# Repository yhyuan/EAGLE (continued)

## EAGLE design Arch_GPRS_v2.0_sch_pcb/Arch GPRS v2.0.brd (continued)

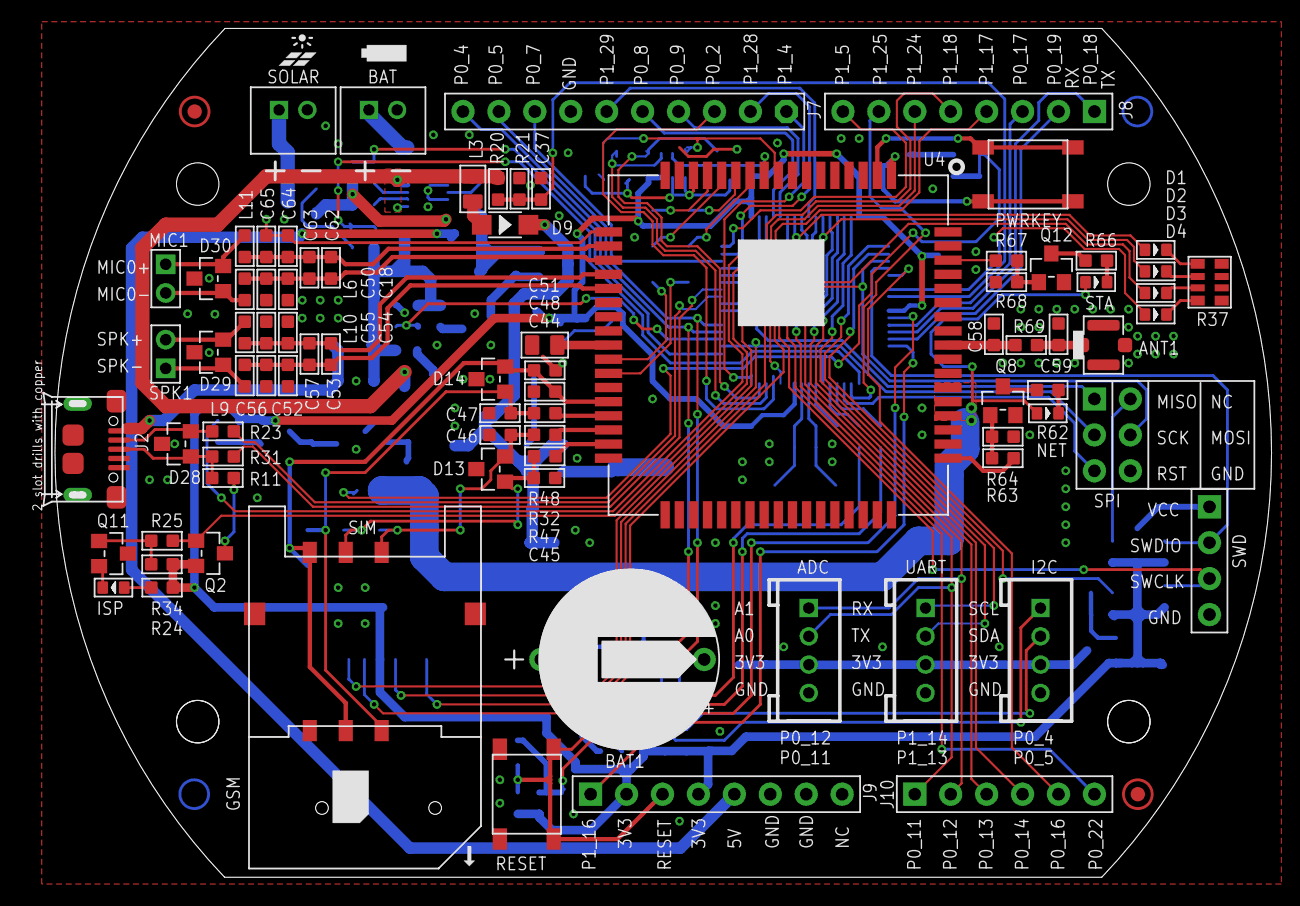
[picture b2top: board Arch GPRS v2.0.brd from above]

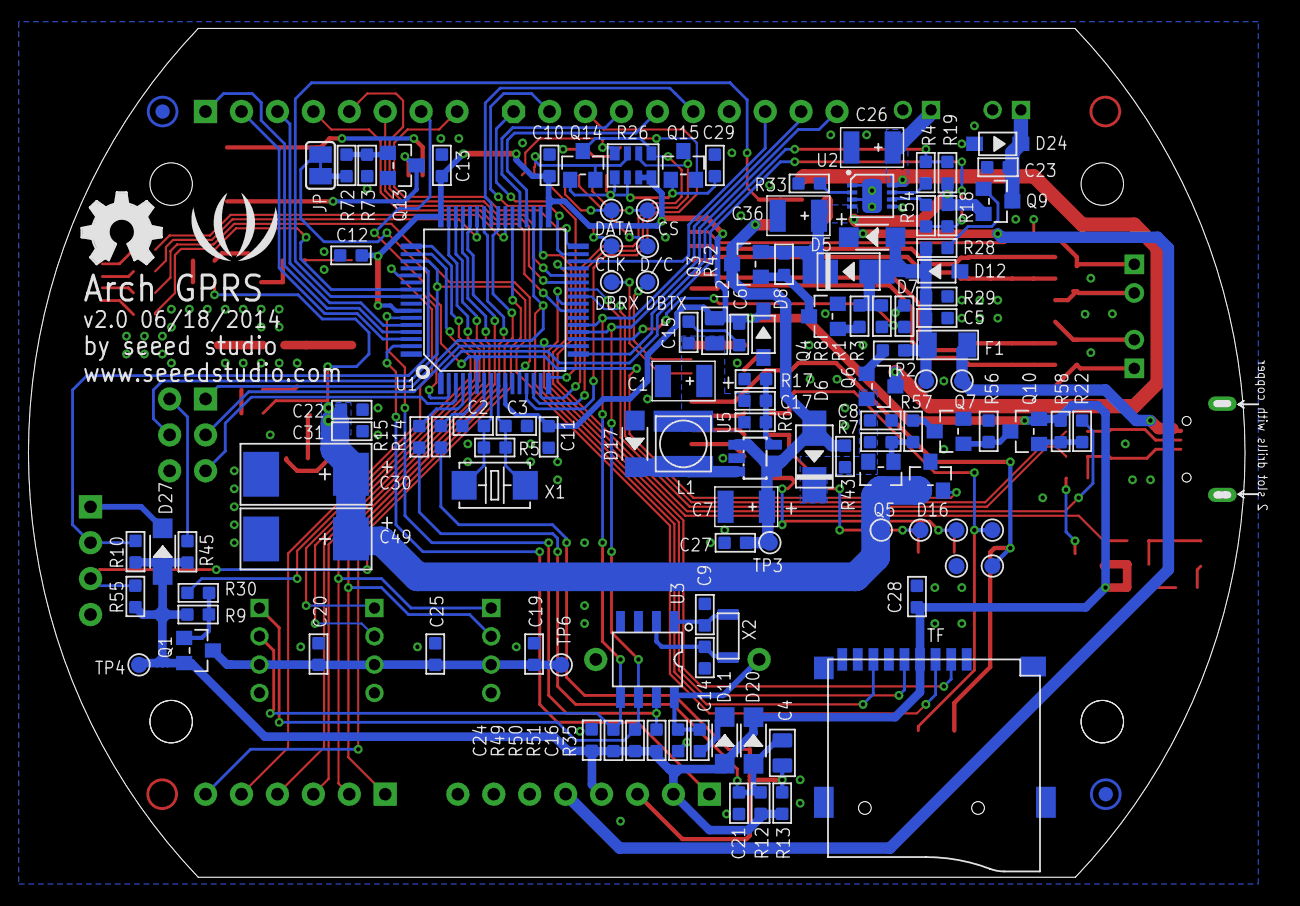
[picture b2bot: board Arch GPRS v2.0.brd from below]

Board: 2 copper layers, 86.9 x 60.0 mm, 207 parts (123 on the bottom side), 139 nets.

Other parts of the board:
U$55: LOGO_SILK
U$56: OSHW_FILLX200_NOTEXT

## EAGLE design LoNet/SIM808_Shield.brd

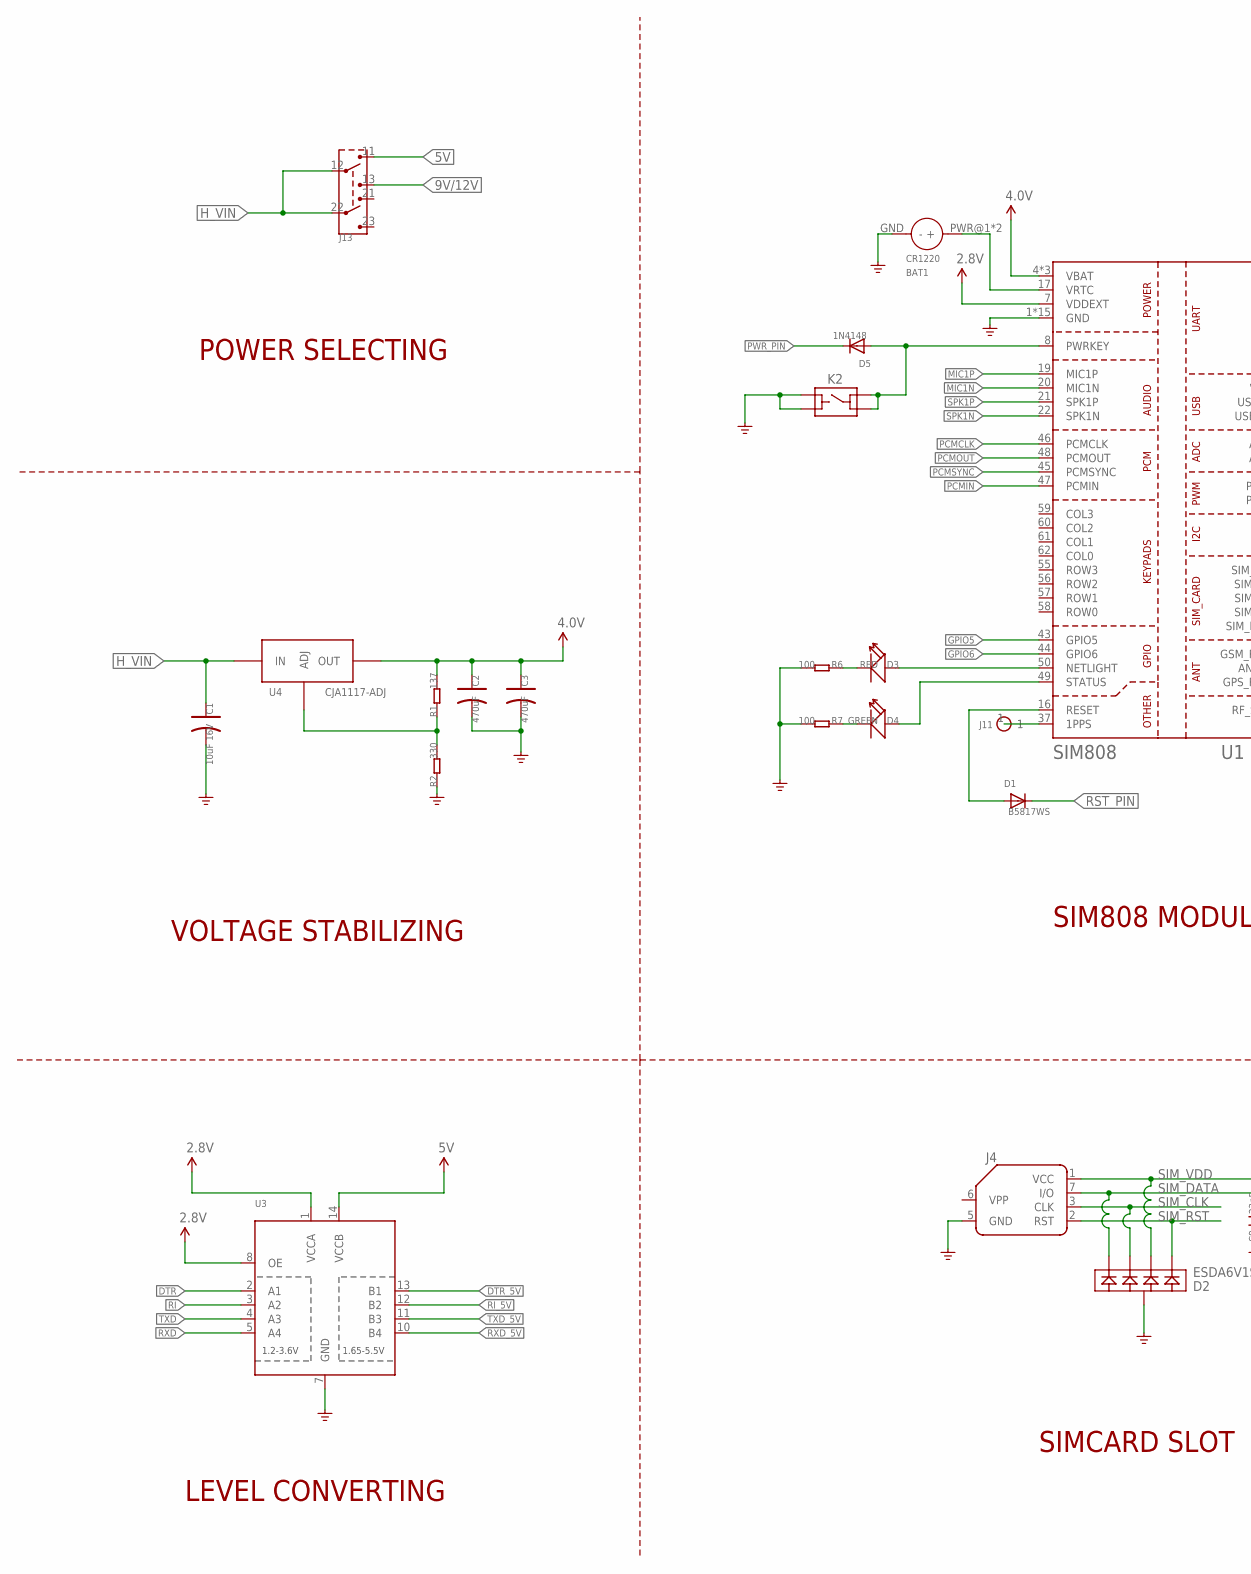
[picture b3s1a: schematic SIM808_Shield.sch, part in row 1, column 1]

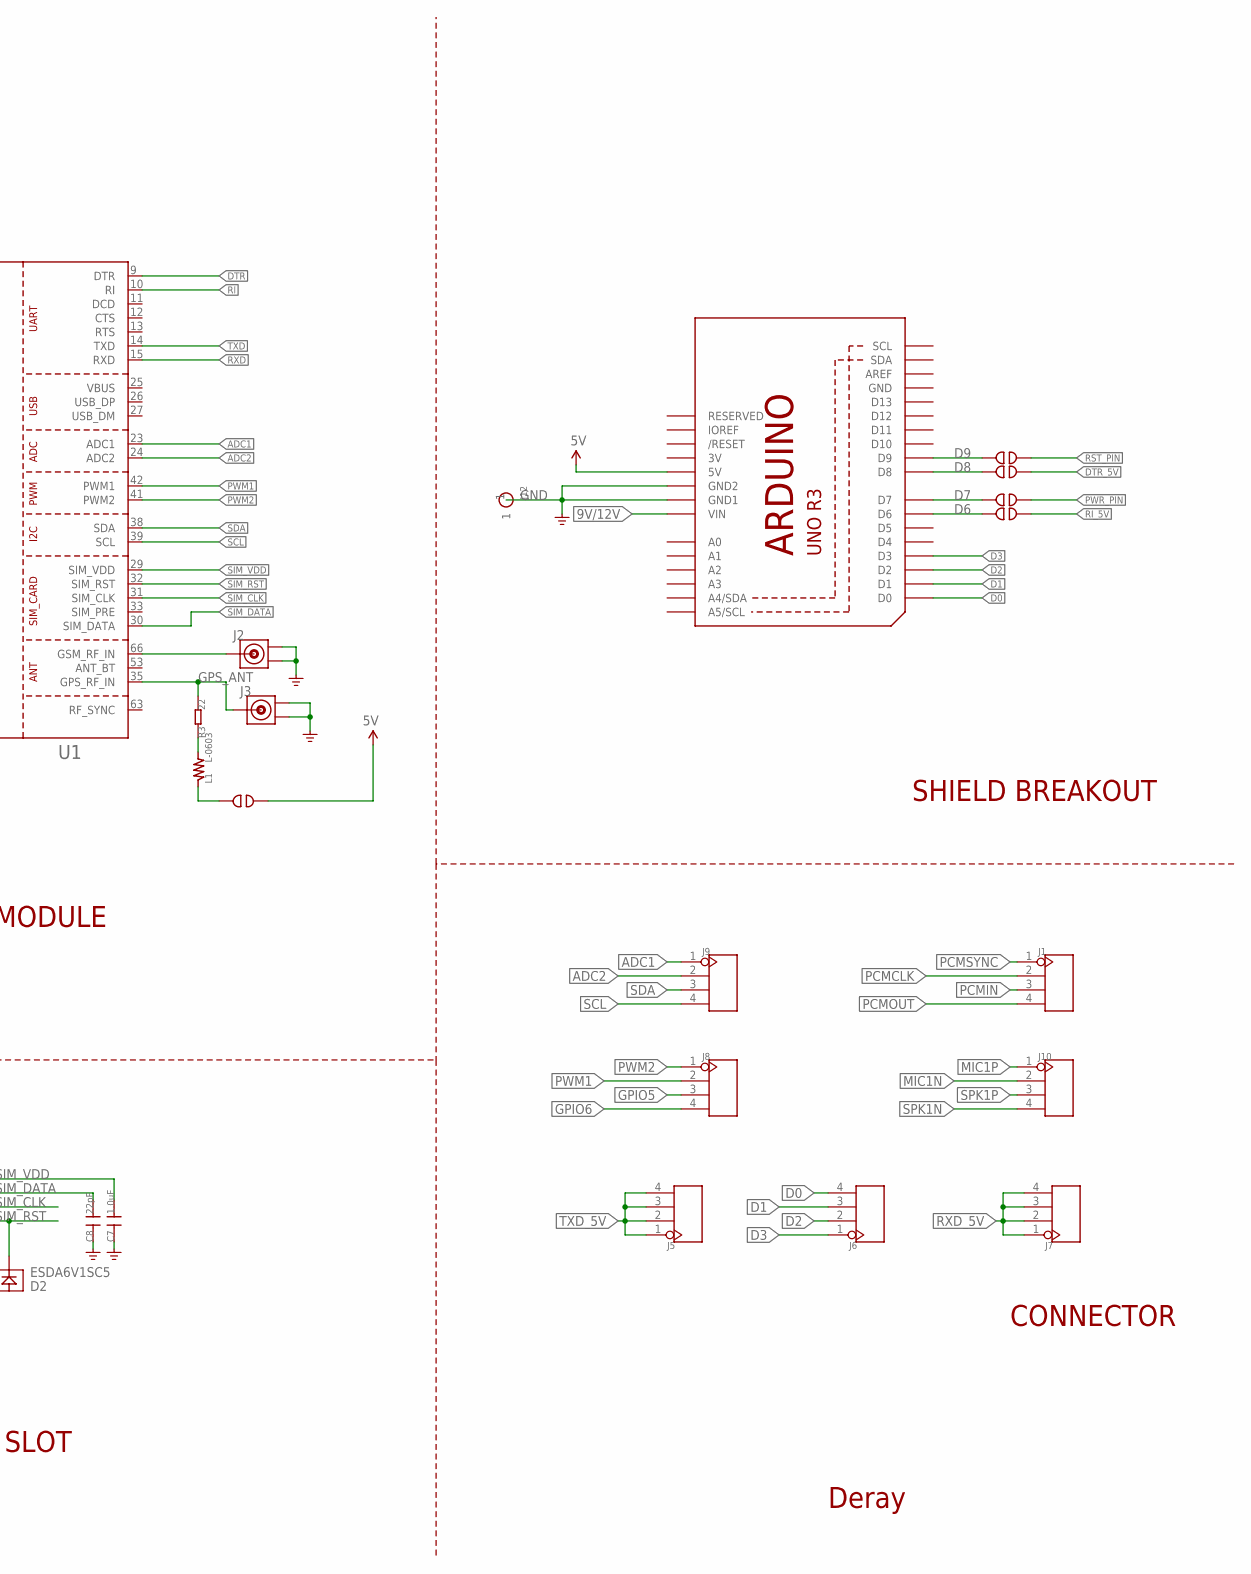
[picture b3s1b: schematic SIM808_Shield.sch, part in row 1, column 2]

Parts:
BAT1: CR1220; BATTCON_12MM
C1: 10uF 16V; AVX-A
C2, C3: 470uF; AVX-D
C7: 1.0uF; 0603
C8: 22pF; 0603
D1: B5817WS; SOD-323F
D2: ESDA6V1SC5; SOT23-5L
D3: RED; 0603
D4: GREEN; 0603
D5: 1N4148; SOD-323F
J1, J5, J6, J7, J8, J9, J10: HEADER-4P-80/40MIL; 4P-2.54-80/40MIL
J2, J3: ANTENNA-U-FL'3PAD-TYPE'; 3P-U-FL
J4: SIMHOLDERSIM; SIMHOLDER
J11, J12: HEADER-1P-40; 1P-80/40MIL
J13: SWITCH-6P-SMD
K2: BUTTON-4P-6X6-SMD; 4P-SMD-6.2X6.2X4H
L1: L-0603; 0603
R1: 137; 0603
R2: 330; 0603
R3: 22; 0603
R6, R7: 100; 0603
U1: SIM808; 68P-24X24X2.6
U2: ARDUINOR3-DIMENSION; ARDUINOR3
U3: TXB0104PWR; TSSOP14
U4: CJA1117-ADJ; SOT89
U$8, U$17, U$18, U$19, U$20: 2P-DISABLE

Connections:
2.8V: U1.7 (VDDEXT), U3.1 (VCCA), U3.8 (OE)
3V: U2.3V
4.0V: C2.+, C3.+, R1.2, U1.4 (VBAT), U1.5 (VBAT), U1.6 (VBAT), U4.2 (OUT), U4.4 (OUT)
5V: J13.11, U2.5V, U3.14 (VCCB), U$17.P$2
9V/12V: J13.13, U2.VIN
ADC1: J9.1, U1.23 (ADC1)
ADC2: J9.2, U1.24 (ADC2)
D0: J6.4, U2.D0
D1: J6.3, U2.D1
D2: J6.2, U2.D2
D3: J6.1, U2.D3
D6: U2.D6, U$20.P$1
D7: U2.D7, U$19.P$1
D8: U2.D8, U$18.P$1
D9: U2.D9, U$8.P$1
DTR: U1.9 (DTR), U3.2 (A1)
DTR_5V: U3.13 (B1), U$18.P$2
GND: BAT1.GND (-), C1.-, C2.-, C3.-, C7.1, C8.1, D2.2, J2.GND1, J2.GND2, J3.GND1, J3.GND2, J4.5 (GND), J12.1, K2.2 (B0), K2.3 (B1), R2.1, R6.2, R7.2, U1.1 (GND), U1.2 (GND), U1.3 (GND), U1.18 (GND), U1.28 (GND), U1.34 (GND), U1.36 (GND), U1.40 (GND), U1.51 (GND), U1.52 (GND), U1.54 (GND), U1.64 (GND), U1.65 (GND), U1.67 (GND), U1.68 (GND), U2.GND, U2.GND1, U2.GND2, U3.7 (GND)
GPIO5: J8.3, U1.43 (GPIO5)
GPIO6: J8.4, U1.44 (GPIO6)
GPS_ANT: J3.D, R3.2, U1.35 (GPS_RF_IN)
H_VIN: C1.+, J13.12, J13.22, U4.3 (IN)
MIC1N: J10.2, U1.20 (MIC1N)
MIC1P: J10.1, U1.19 (MIC1P)
unnamed: BAT1.PWR@1 (+), BAT1.PWR@2 (+), U1.17 (VRTC)
unnamed: J2.D, U1.66 (GSM_RF_IN)
unnamed: R1.1, R2.2, U4.1 (ADJ)
unnamed: D1.A, U1.16 (RESET)
unnamed: J11.1, U1.37 (1PPS)
unnamed: D4.-, R7.1
unnamed: D5.A, K2.1 (A0), K2.4 (A1), U1.8 (PWRKEY)
unnamed: D3.-, R6.1
unnamed: D4.+, U1.49 (STATUS)
unnamed: D3.+, U1.50 (NETLIGHT)
unnamed: L1.1, U$17.P$1
unnamed: L1.2, R3.1
PCMCLK: J1.2, U1.46 (PCMCLK)
PCMIN: J1.3, U1.47 (PCMIN)
PCMOUT: J1.4, U1.48 (PCMOUT)
PCMSYNC: J1.1, U1.45 (PCMSYNC)
PWM1: J8.2, U1.42 (PWM1)
PWM2: J8.1, U1.41 (PWM2)
PWR_PIN: D5.C, U$19.P$2
RI: U1.10 (RI), U3.3 (A2)
RI_5V: U3.12 (B2), U$20.P$2
RST_PIN: D1.C, U$8.P$2
RXD: U1.15 (RXD), U3.5 (A4)
RXD_5V: J7.1, J7.2, J7.3, J7.4, U3.10 (B4)
SCL: J9.4, U1.39 (SCL)
SDA: J9.3, U1.38 (SDA)
SIM_CLK: D2.3, J4.3 (CLK), U1.31 (SIM_CLK)
SIM_DATA: C8.2, D2.1, J4.7 (I/O), U1.30 (SIM_DATA)
SIM_RST: D2.4, J4.2 (RST), U1.32 (SIM_RST)
SIM_VDD: C7.2, D2.5, J4.1 (VCC), U1.29 (SIM_VDD)
SPK1N: J10.4, U1.22 (SPK1N)
SPK1P: J10.3, U1.21 (SPK1P)
TXD: U1.14 (TXD), U3.4 (A3)
TXD_5V: J5.1, J5.2, J5.3, J5.4, U3.11 (B3)

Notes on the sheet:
POWER SELECTING
LEVEL CONVERTING
SIMCARD SLOT
SIM808 MODULE
CONNECTOR
SHIELD BREAKOUT
VOLTAGE STABILIZING
Deray

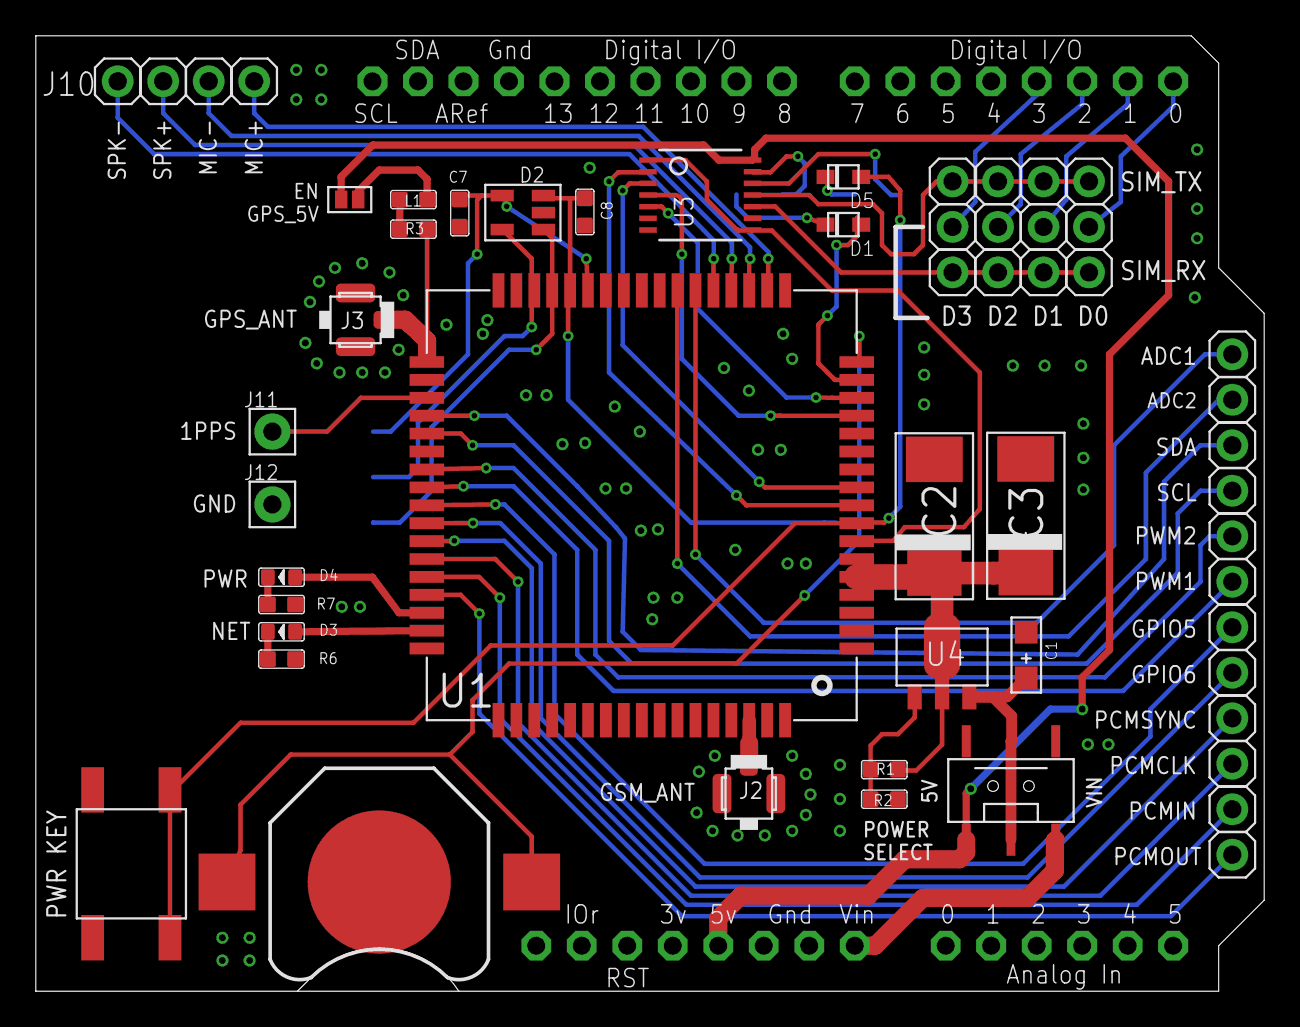
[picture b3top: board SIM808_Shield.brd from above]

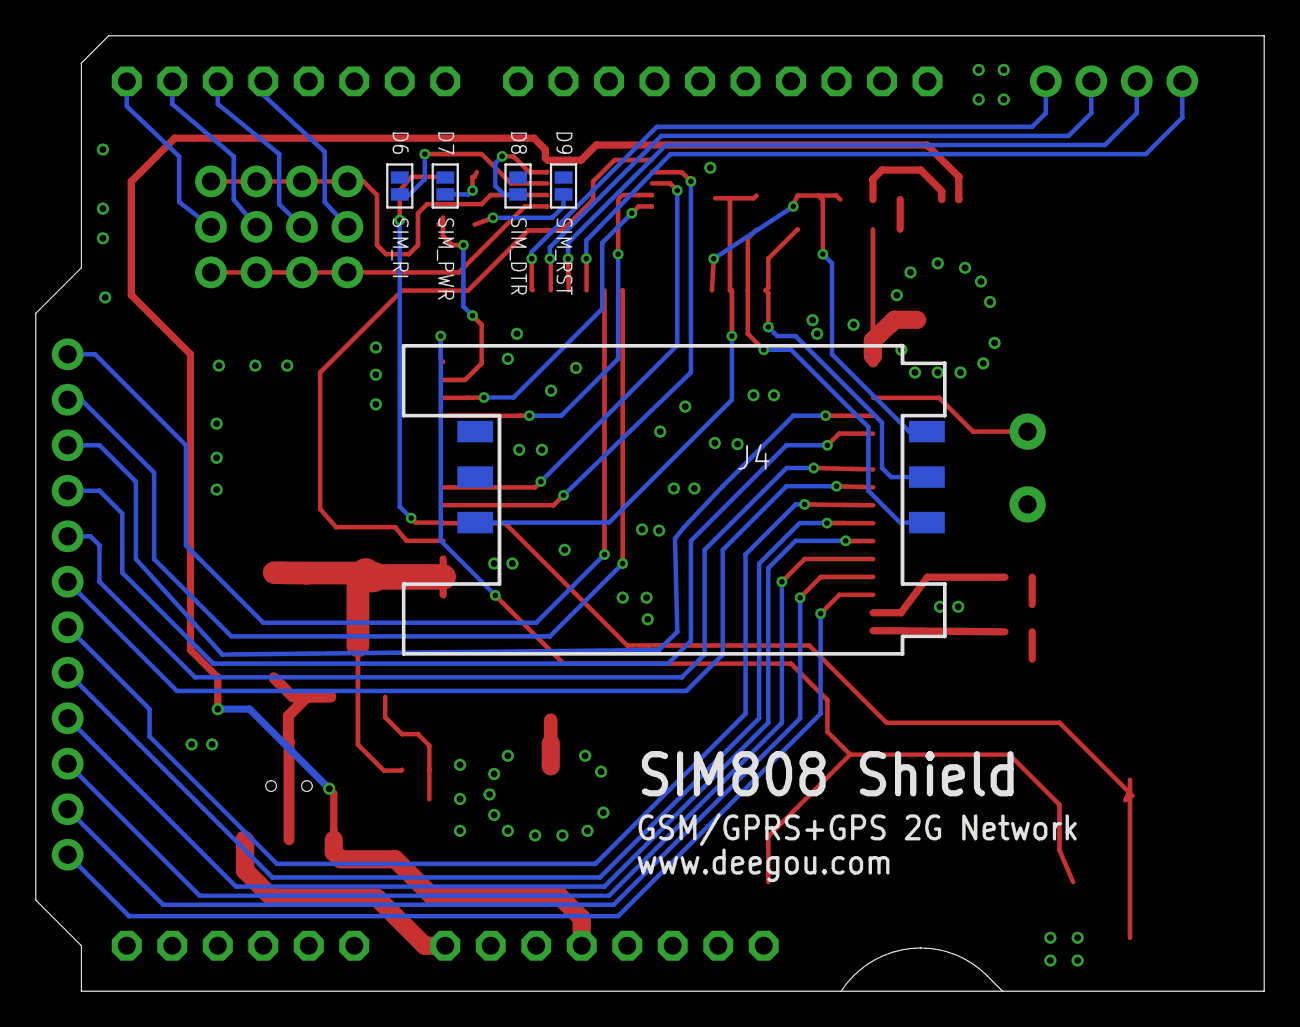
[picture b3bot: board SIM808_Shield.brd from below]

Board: 2 copper layers, 68.6 x 53.3 mm, 40 parts (5 on the bottom side), 57 nets.

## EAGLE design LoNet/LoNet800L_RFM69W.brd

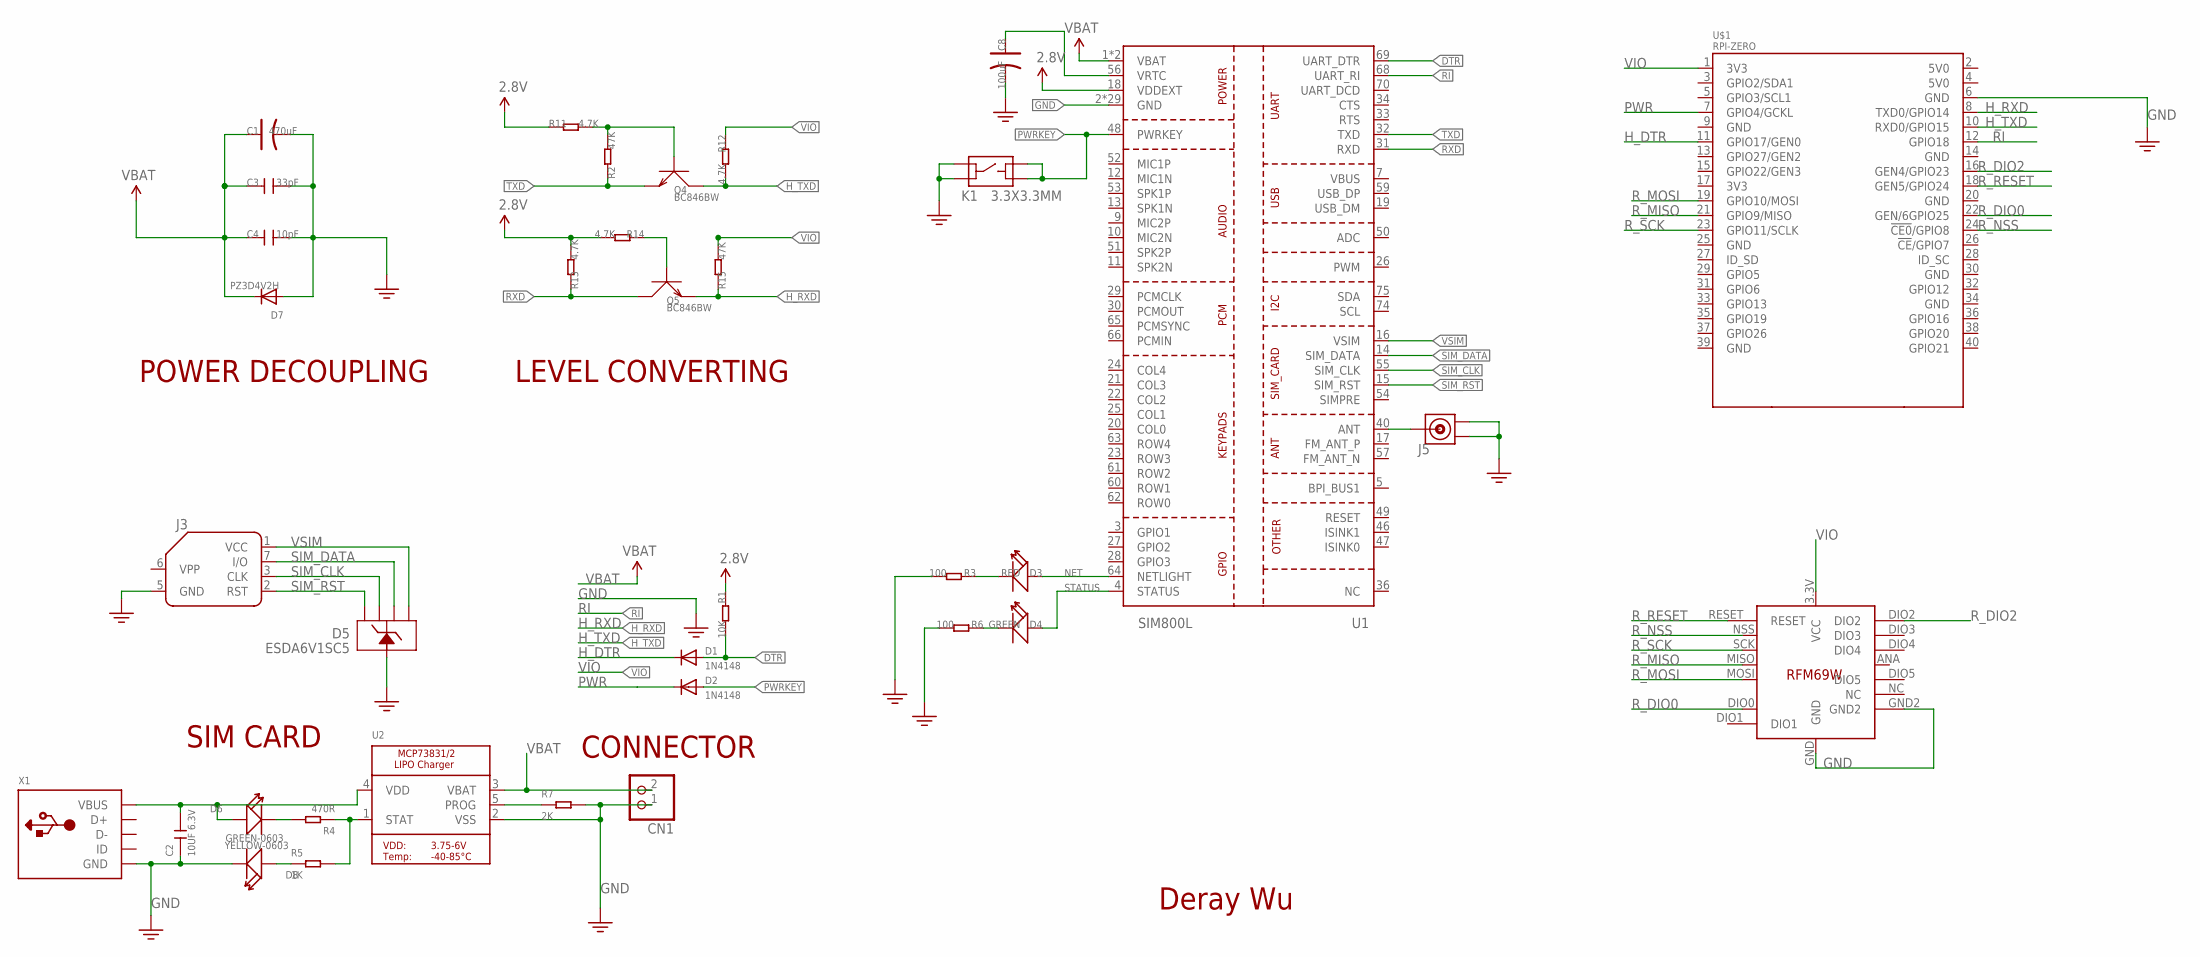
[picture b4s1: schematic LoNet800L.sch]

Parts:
C1: 470uF; AVX-D
C2: 10UF 6.3V; C0603
C3: 33pF; C0603
C4: 10pF; C0603
C8: 100uF; AVX-A
CN1: JST_2PIN; JSTPH2
D1, D2: 1N4148; SOD-323F
D3: RED; 0603
D4: GREEN; 0603
D5: ESDA6V1SC5; SOT23-5L
D6: YELLOW-0603; LED-0603
D7: PZ3D4V2H; SOD-323F
D8: GREEN-0603; LED-0603
J3: SIMHOLDERSIM; SIMHOLDER
J5: ANTENNA-U-FL'3PAD-TYPE'; 3P-U-FL
K1: 3.3X3.3MM; 4P-SMD-3.4X3.4X1.3H
Q4, Q5: BC846BW; SOT323
R1: 10K; 0603
R2, R15: 47K; 0603
R3, R6: 100; 0603
R4: 470R; R0603
R5: 1K; R0603
R7: 2K; R0603
R11, R12, R13, R14: 4.7K; 0603
U1: SIM800L; 88P-17.8X15.8X2.4
U2: MCP73831/2; SOT23-5
U$1: RPI-ZERO; RASPBERRYPI_BASTELSTUBE_V13_RASPI_BOARD_B+_FULL
U$2: RFM69; RFM69W-MINPADS
X1: USBMICRO_20329; 4UCONN_20329

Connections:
2.8V: R1.1, R11.1, R13.2, R14.2, U1.18 (VDDEXT)
ANT: J5.D, U1.40 (ANT)
DTR: D1.A, R1.2, U1.69 (UART_DTR)
GND: C1.-, C2.1, C3.2, C4.2, C8.-, CN1.1, D5.2, D7.A, D8.-, J3.5 (GND), J5.GND1, J5.GND2, K1.A0, K1.A1, R3.2, R6.2, R7.2, U1.2 (GND), U1.6 (GND), U1.8 (GND), U1.35 (GND), U1.37 (GND), U1.38 (GND), U1.39 (GND), U1.41 (GND), U1.43 (GND), U1.44 (GND), U1.45 (GND), U1.58 (GND), U1.67 (GND), U1.71 (GND), U1.72 (GND), U1.73 (GND), U1.76 (GND), U1.77 (GND), U1.78 (GND), U1.79 (GND), U1.80 (GND), U1.81 (GND), U1.82 (GND), U1.83 (GND), U1.84 (GND), U1.85 (GND), U1.86 (GND), U1.87 (GND), U1.88 (GND), U2.2 (VSS), U$1.6 (GND), U$2.GND, U$2.GND2, X1.BASE@1 (GND), X1.BASE@2 (GND), X1.GND, X1.SPRT@1 (GND), X1.SPRT@2 (GND), X1.SPRT@3 (GND), X1.SPRT@4 (GND)
H_DTR: D1.C, U$1.11 (GPIO17/GEN0)
H_RXD: Q5.2 (E), R15.1, U$1.8 (TXD0/GPIO14)
H_TXD: Q4.3 (C), R12.2, U$1.10 (RXD0/GPIO15)
unnamed: C8.+, U1.56 (VRTC)
unnamed: C2.2, D6.+, U2.4 (VDD), X1.VBUS
unnamed: D3.-, R3.1
unnamed: D6.-, R4.2
unnamed: Q4.1 (B), R2.2, R11.2
unnamed: R4.1, R5.2, U2.1 (STAT)
unnamed: D4.-, R6.1
unnamed: Q5.1 (B), R14.1
unnamed: D8.+, R5.1
unnamed: R7.1, U2.5 (PROG)
NET: D3.+, U1.64 (NETLIGHT)
PWR: D2.C, U$1.7 (GPIO4/GCKL)
PWRKEY: D2.A, K1.B0, K1.B1, U1.48 (PWRKEY)
RI: U1.68 (UART_RI), U$1.12 (GPIO18)
RXD: Q5.3 (C), R13.1, U1.31 (RXD)
R_DIO0: U$1.22 (GEN/6GPIO25), U$2.DIO0
R_DIO2: U$1.16 (GEN4/GPIO23), U$2.DIO2
R_MISO: U$1.21 (GPIO9/MISO), U$2.MISO
R_MOSI: U$1.19 (GPIO10/MOSI), U$2.MOSI
R_NSS: U$1.24 (!CE0!/GPIO8), U$2.NSS (SEL)
R_RESET: U$1.18 (GEN5/GPIO24), U$2.RESET
R_SCK: U$1.23 (GPIO11/SCLK), U$2.SCK
SIM_CLK: D5.5, J3.3 (CLK), U1.55 (SIM_CLK)
SIM_DATA: D5.3, J3.7 (I/O), U1.14 (SIM_DATA)
SIM_RST: D5.4, J3.2 (RST), U1.15 (SIM_RST)
STATUS: D4.+, U1.4 (STATUS)
TXD: Q4.2 (E), R2.1, U1.32 (TXD)
VBAT: C1.+, C3.1, C4.1, CN1.2, D7.C, U1.1 (VBAT), U1.42 (VBAT), U2.3 (VBAT)
VIO: R12.1, R15.2, U$1.1 (3V3), U$2.3.3V (VCC)
VSIM: D5.1, J3.1 (VCC), U1.16 (VSIM)

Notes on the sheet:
SIM CARD
POWER DECOUPLING
Deray Wu
CONNECTOR
LEVEL CONVERTING

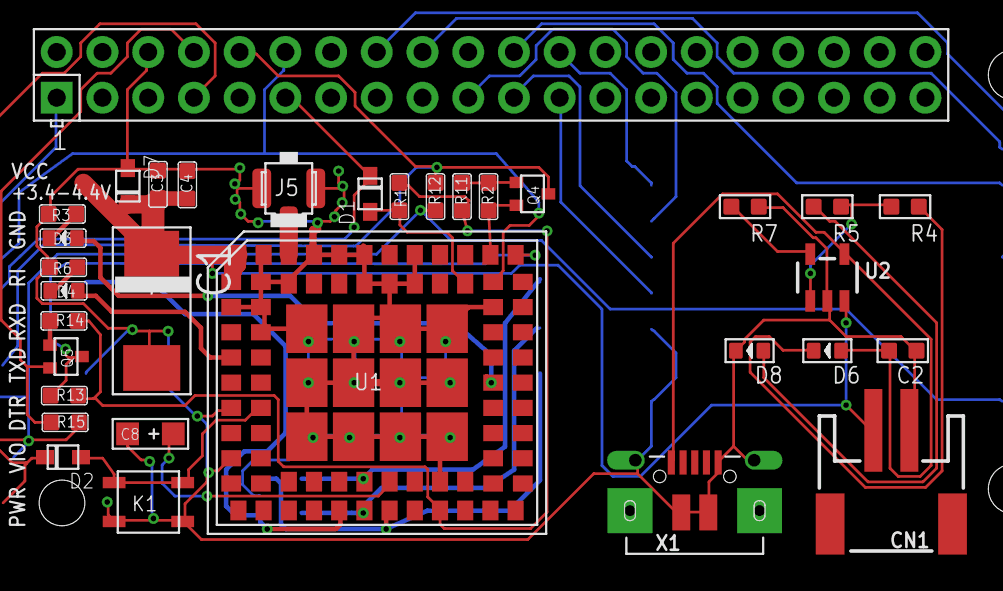
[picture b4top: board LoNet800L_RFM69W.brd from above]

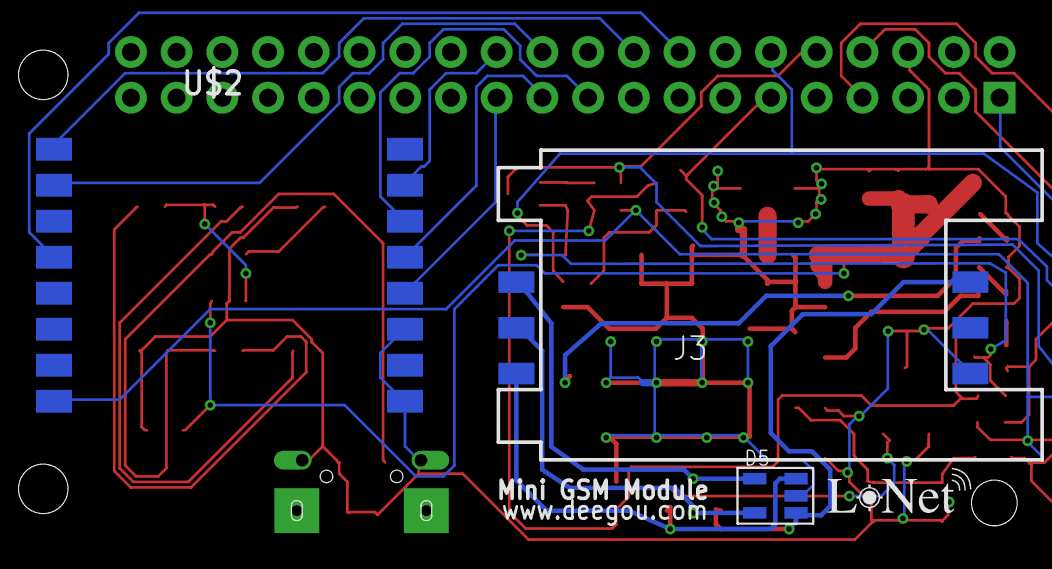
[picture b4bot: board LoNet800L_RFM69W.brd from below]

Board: 4 copper layers, 36 parts (3 on the bottom side), 37 nets.

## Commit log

2015-11-20 add new designs
2015-11-20 boards
2015-11-26 add more GPRS shields
2015-11-26 Moteino shield
2015-11-27 add more designs
2015-12-03 add mroe boards
2015-12-03 add arminarm pinout
2015-12-08 add something
2015-12-09 fona board
2015-12-17 Edit Lonet
2015-12-17 Change LoNet 800L with RFM69 and batter recharger
2015-12-18 add boards
